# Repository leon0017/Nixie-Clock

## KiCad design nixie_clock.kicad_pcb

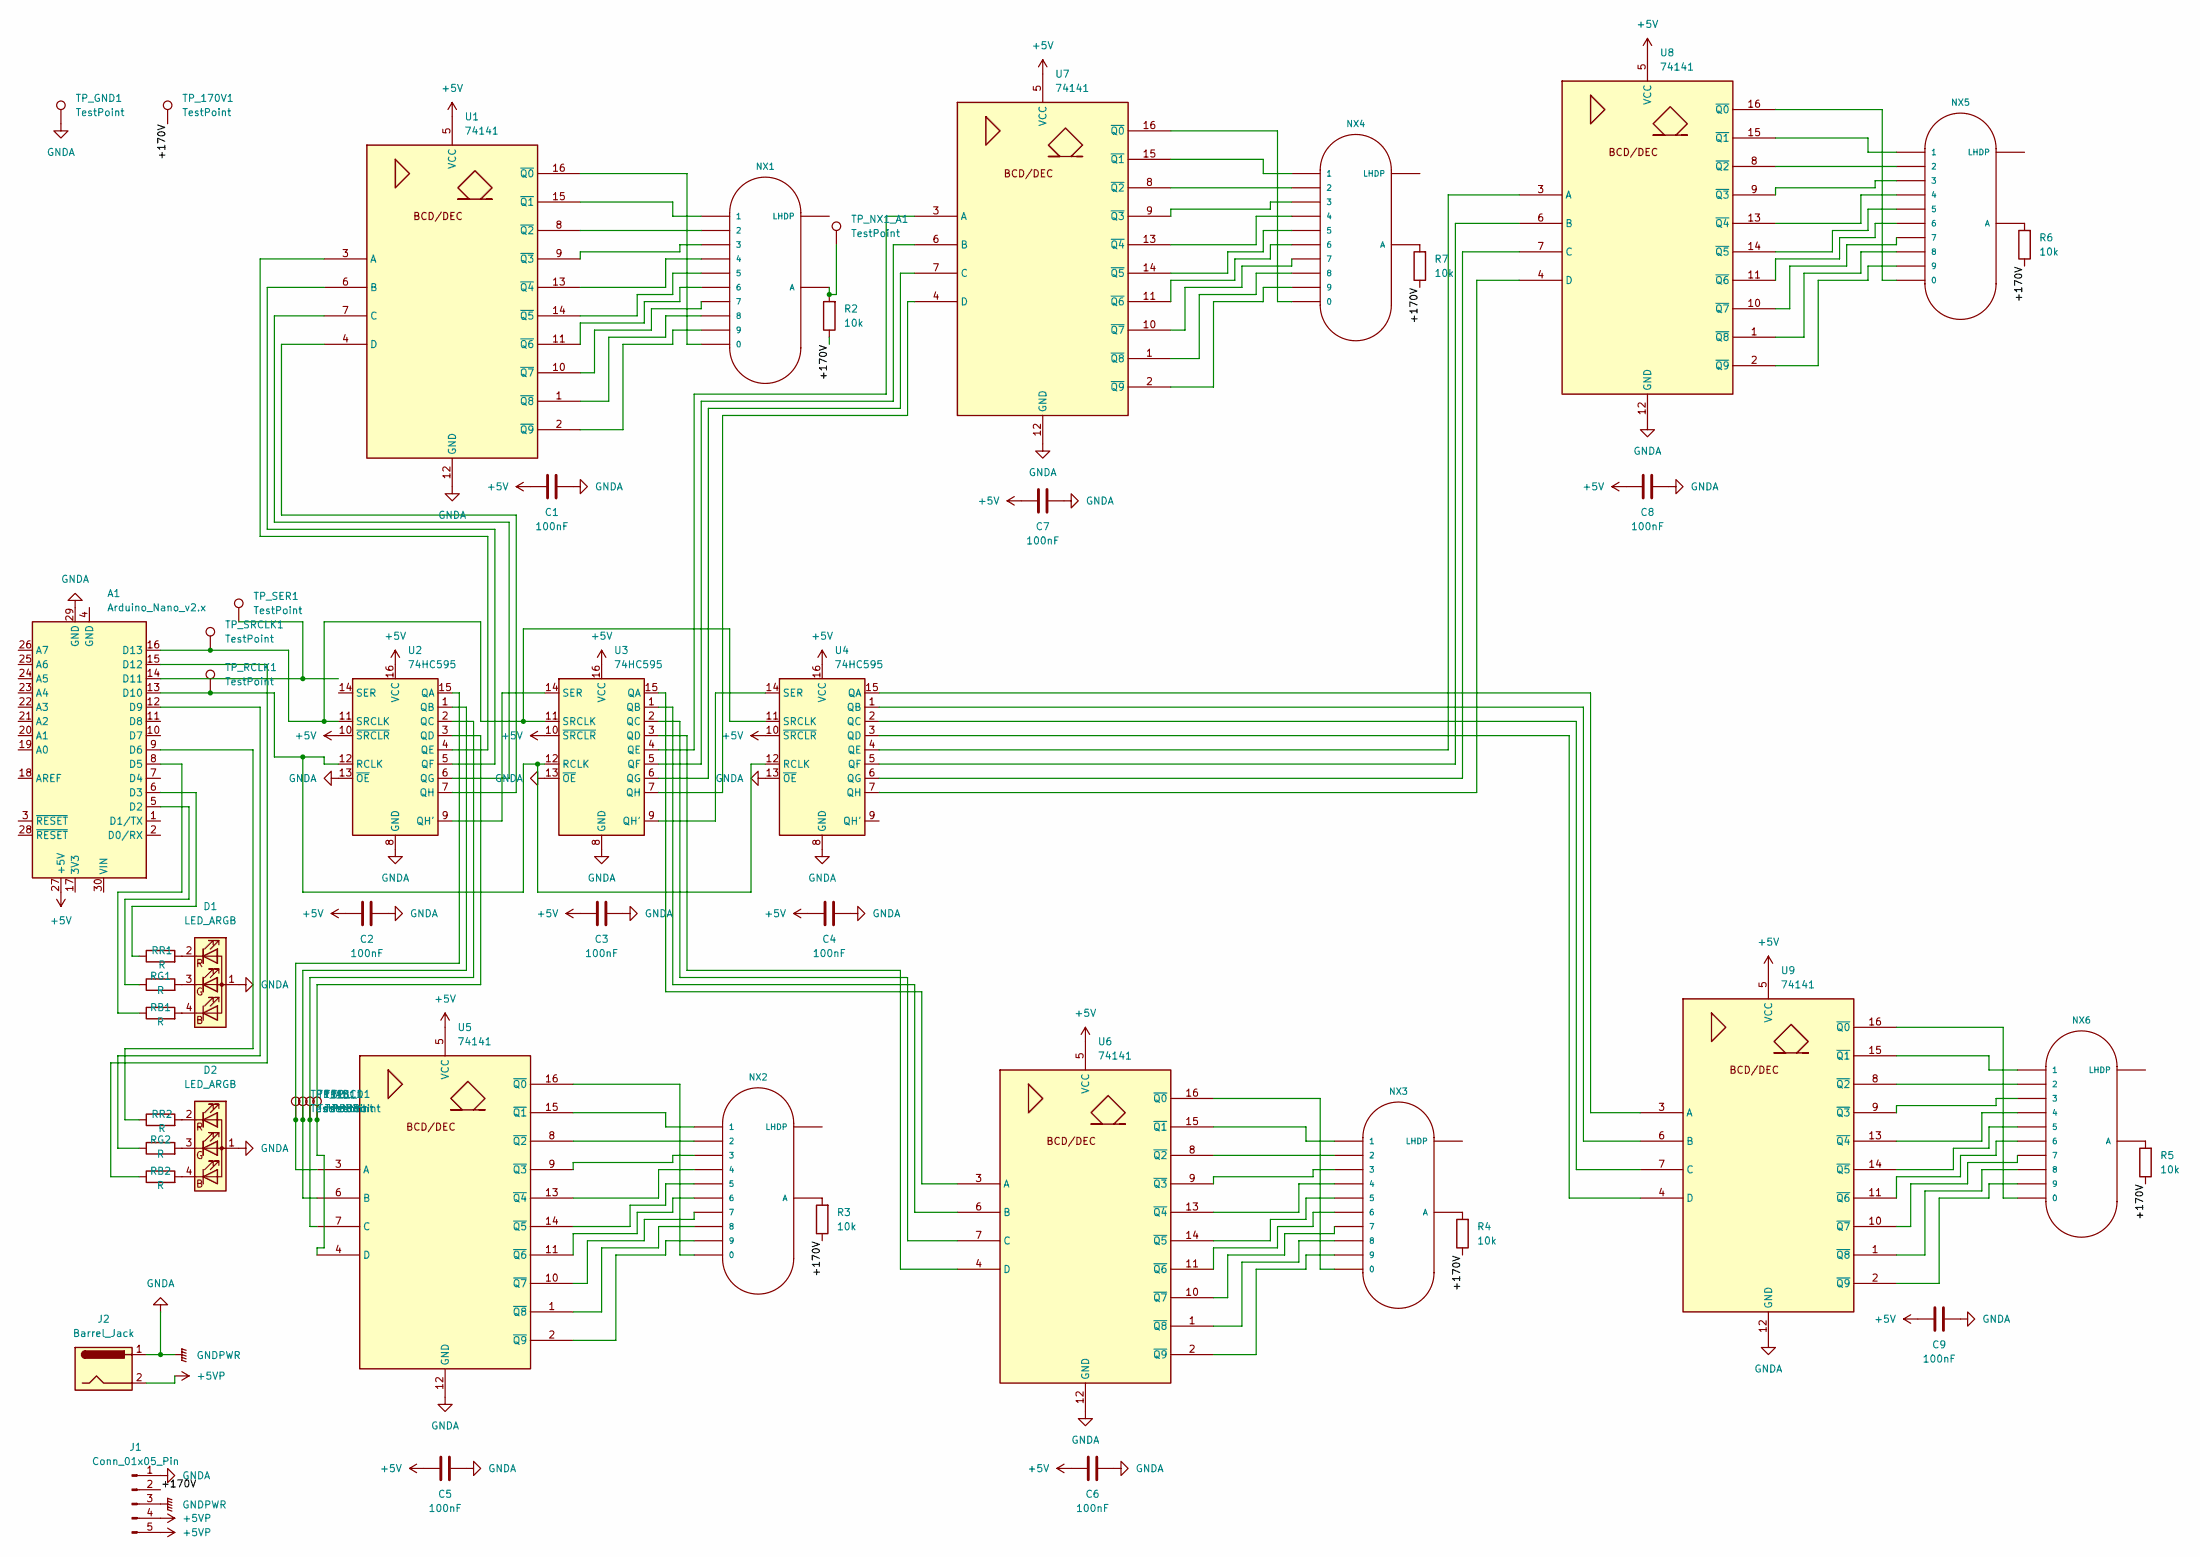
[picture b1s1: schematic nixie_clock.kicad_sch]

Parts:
A1: Arduino_Nano_v2.x; Arduino_Nano
C1, C2, C3, C4, C5, C6, C7, C8, C9: 100nF; C_Disc_D5.0mm_W2.5mm_P5.00mm
D1, D2: LED_ARGB; LED_D5.0mm-4_RGB
J1: Conn_01x05_Pin; AliStepUp
J2: Barrel_Jack; BarrelJack_Horizontal
NX1, NX2, NX3, NX4, NX5, NX6: IN-12BORIGINAL; nixies-us-IN-12
R2, R3, R4, R5, R6, R7: 10k; R_Axial_DIN0207_L6.3mm_D2.5mm_P10.16mm_Horizontal
RB1, RB2: R; R_Axial_DIN0207_L6.3mm_D2.5mm_P10.16mm_Horizontal
RG1, RG2: R; R_Axial_DIN0207_L6.3mm_D2.5mm_P10.16mm_Horizontal
RR1, RR2: R; R_Axial_DIN0207_L6.3mm_D2.5mm_P10.16mm_Horizontal
TP1_A1, TP1_B1, TP1_C1, TP1_D1: TestPoint; TestPoint_Pad_D1.0mm
TP_170V1: TestPoint; TestPoint_Pad_D1.0mm
TP_GND1: TestPoint; TestPoint_Pad_D1.0mm
TP_NX1_A1: TestPoint; TestPoint_Pad_D1.0mm
TP_RCLK1: TestPoint; TestPoint_Pad_D1.0mm
TP_SER1: TestPoint; TestPoint_Pad_D1.0mm
TP_SRCLK1: TestPoint; TestPoint_Pad_D1.0mm
U1, U5, U6, U7, U8, U9: 74141; DIP-16_W7.62mm
U2, U3, U4: 74HC595; DIP-16_W7.62mm

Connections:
+5V: A1.27 (+5V), C1.1, C2.1, C3.1, C4.1, C5.1, C6.1, C7.1, C8.1, C9.1, U1.5 (VCC), U2.10 (~SRCLR), U2.16 (VCC), U3.10 (~SRCLR), U3.16 (VCC), U4.10 (~SRCLR), U4.16 (VCC), U5.5 (VCC), U6.5 (VCC), U7.5 (VCC), U8.5 (VCC), U9.5 (VCC)
+5VP: J1.4, J1.5, J2.2
/+170V: J1.2, R2.1, R3.1, R4.1, R5.1, R6.1, R7.1, TP_170V1.1 (1_1)
GNDA: A1.29 (GND), C1.2, C2.2, C3.2, C4.2, C5.2, C6.2, C7.2, C8.2, C9.2, D1.1 (A), D2.1 (A), J1.1, J1.3, J2.1, TP_GND1.1 (1_1), U1.12 (GND), U2.8 (GND), U2.13 (~OE), U3.8 (GND), U3.13 (~OE), U4.8 (GND), U4.13 (~OE), U5.12 (GND), U6.12 (GND), U7.12 (GND), U8.12 (GND), U9.12 (GND)
unnamed: A1.5 (D2), RG1.1
unnamed: A1.6 (D3), RR1.1
unnamed: A1.8 (D5), RB1.1
unnamed: A1.9 (D6), RR2.1
unnamed: A1.12 (D9), RG2.1
unnamed: A1.13 (D10), TP_RCLK1.1 (1_1), U2.12 (RCLK), U3.12 (RCLK), U4.12 (RCLK)
unnamed: A1.14 (D11), TP_SER1.1 (1_1)
unnamed: A1.15 (D12), RB2.1
unnamed: A1.16 (D13), TP_SRCLK1.1 (1_1), U2.11 (SRCLK), U3.11 (SRCLK), U4.11 (SRCLK)
unnamed: D1.4 (BK), RB1.2
unnamed: D1.3 (GK), RG1.2
unnamed: D1.2 (RK), RR1.2
unnamed: D2.4 (BK), RB2.2
unnamed: D2.3 (GK), RG2.2
unnamed: D2.2 (RK), RR2.2
unnamed: NX1.A, R2.2, TP_NX1_A1.1 (1_1)
unnamed: NX2.A, R3.2
unnamed: NX3.A, R4.2
unnamed: NX4.A, R7.2
unnamed: NX5.A, R6.2
unnamed: NX6.A, R5.2
unnamed: U1.3 (A), U2.4 (QE)
unnamed: U1.6 (B), U2.5 (QF)
unnamed: U1.7 (C), U2.6 (QG)
unnamed: U1.4 (D), U2.7 (QH)
unnamed: NX1.0, U1.16 (~Q0)
unnamed: NX1.1, U1.15 (~Q1)
unnamed: NX1.2, U1.8 (~Q2)
unnamed: NX1.3, U1.9 (~Q3)
unnamed: NX1.4, U1.13 (~Q4)
unnamed: NX1.5, U1.14 (~Q5)
unnamed: NX1.6, U1.11 (~Q6)
unnamed: NX1.7, U1.10 (~Q7)
unnamed: NX1.8, U1.1 (~Q8)
unnamed: NX1.9, U1.2 (~Q9)
unnamed: TP1_A1.1 (1_1), U2.15 (QA), U5.3 (A)
unnamed: TP1_B1.1 (1_1), U2.1 (QB), U5.6 (B)
unnamed: TP1_C1.1 (1_1), U2.2 (QC), U5.7 (C)
unnamed: TP1_D1.1 (1_1), U2.3 (QD), U5.4 (D)
unnamed: U2.9 (QH'), U3.14 (SER)
unnamed: U3.15 (QA), U6.3 (A)
unnamed: U3.1 (QB), U6.6 (B)
unnamed: U3.2 (QC), U6.7 (C)
unnamed: U3.3 (QD), U6.4 (D)
unnamed: U3.4 (QE), U7.3 (A)
unnamed: U3.5 (QF), U7.6 (B)
unnamed: U3.6 (QG), U7.7 (C)
unnamed: U3.9 (QH'), U4.14 (SER)
unnamed: U3.7 (QH), U7.4 (D)
unnamed: U4.15 (QA), U9.3 (A)
unnamed: U4.1 (QB), U9.6 (B)
unnamed: U4.2 (QC), U9.7 (C)
unnamed: U4.3 (QD), U9.4 (D)
unnamed: U4.4 (QE), U8.3 (A)
unnamed: U4.5 (QF), U8.6 (B)
unnamed: U4.6 (QG), U8.7 (C)
unnamed: U4.7 (QH), U8.4 (D)
unnamed: NX2.0, U5.16 (~Q0)
unnamed: NX2.1, U5.15 (~Q1)
unnamed: NX2.2, U5.8 (~Q2)
unnamed: NX2.3, U5.9 (~Q3)
unnamed: NX2.4, U5.13 (~Q4)
unnamed: NX2.5, U5.14 (~Q5)
unnamed: NX2.6, U5.11 (~Q6)
unnamed: NX2.7, U5.10 (~Q7)
unnamed: NX2.8, U5.1 (~Q8)
unnamed: NX2.9, U5.2 (~Q9)
unnamed: NX3.0, U6.16 (~Q0)
unnamed: NX3.1, U6.15 (~Q1)
unnamed: NX3.2, U6.8 (~Q2)
unnamed: NX3.3, U6.9 (~Q3)
unnamed: NX3.4, U6.13 (~Q4)
unnamed: NX3.5, U6.14 (~Q5)
unnamed: NX3.6, U6.11 (~Q6)
unnamed: NX3.7, U6.10 (~Q7)
unnamed: NX3.8, U6.1 (~Q8)
unnamed: NX3.9, U6.2 (~Q9)
unnamed: NX4.0, U7.16 (~Q0)
unnamed: NX4.1, U7.15 (~Q1)
unnamed: NX4.2, U7.8 (~Q2)
unnamed: NX4.3, U7.9 (~Q3)
unnamed: NX4.4, U7.13 (~Q4)
unnamed: NX4.5, U7.14 (~Q5)
unnamed: NX4.6, U7.11 (~Q6)
unnamed: NX4.7, U7.10 (~Q7)
unnamed: NX4.8, U7.1 (~Q8)
unnamed: NX4.9, U7.2 (~Q9)
unnamed: NX5.0, U8.16 (~Q0)
unnamed: NX5.1, U8.15 (~Q1)
unnamed: NX5.2, U8.8 (~Q2)
unnamed: NX5.3, U8.9 (~Q3)
unnamed: NX5.4, U8.13 (~Q4)
unnamed: NX5.5, U8.14 (~Q5)
unnamed: NX5.6, U8.11 (~Q6)
unnamed: NX5.7, U8.10 (~Q7)
unnamed: NX5.8, U8.1 (~Q8)
unnamed: NX5.9, U8.2 (~Q9)
unnamed: NX6.0, U9.16 (~Q0)
unnamed: NX6.1, U9.15 (~Q1)
unnamed: NX6.2, U9.8 (~Q2)
unnamed: NX6.3, U9.9 (~Q3)
unnamed: NX6.4, U9.13 (~Q4)
unnamed: NX6.5, U9.14 (~Q5)
unnamed: NX6.6, U9.11 (~Q6)
unnamed: NX6.7, U9.10 (~Q7)
unnamed: NX6.8, U9.1 (~Q8)
unnamed: NX6.9, U9.2 (~Q9)

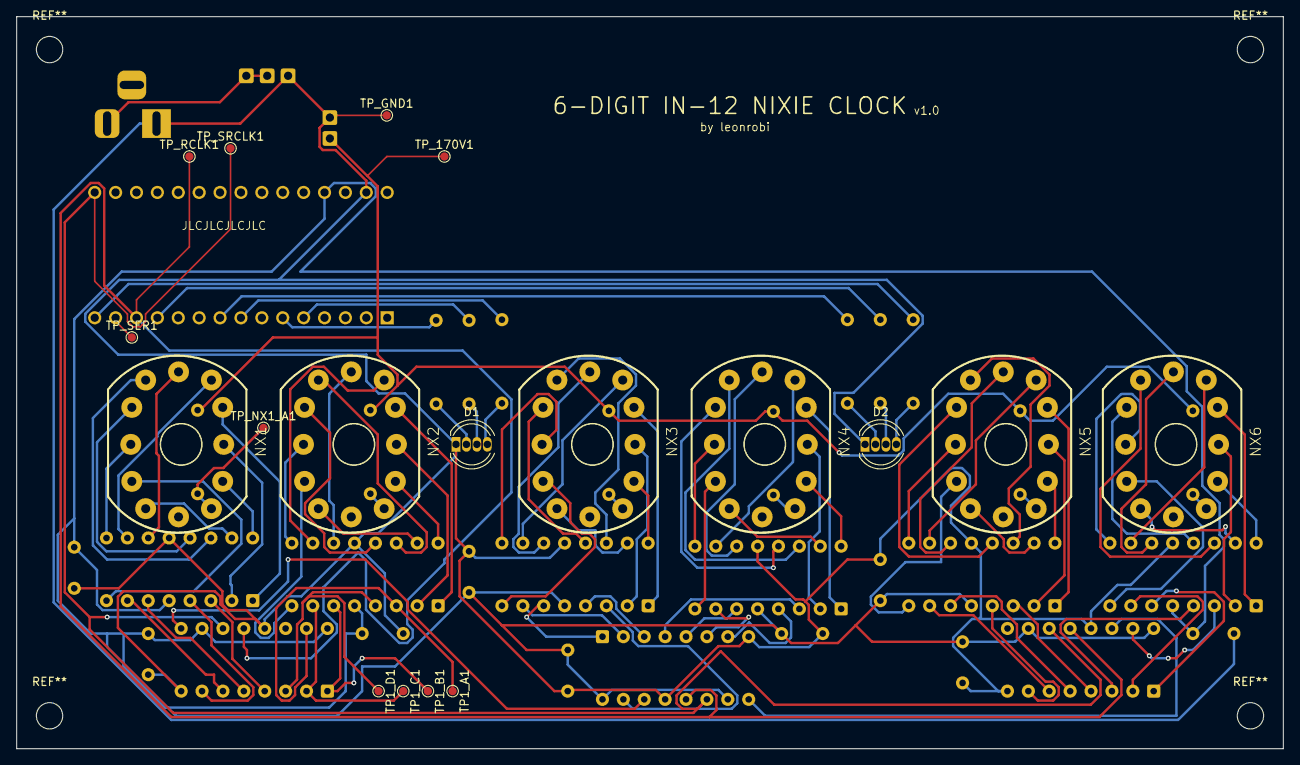
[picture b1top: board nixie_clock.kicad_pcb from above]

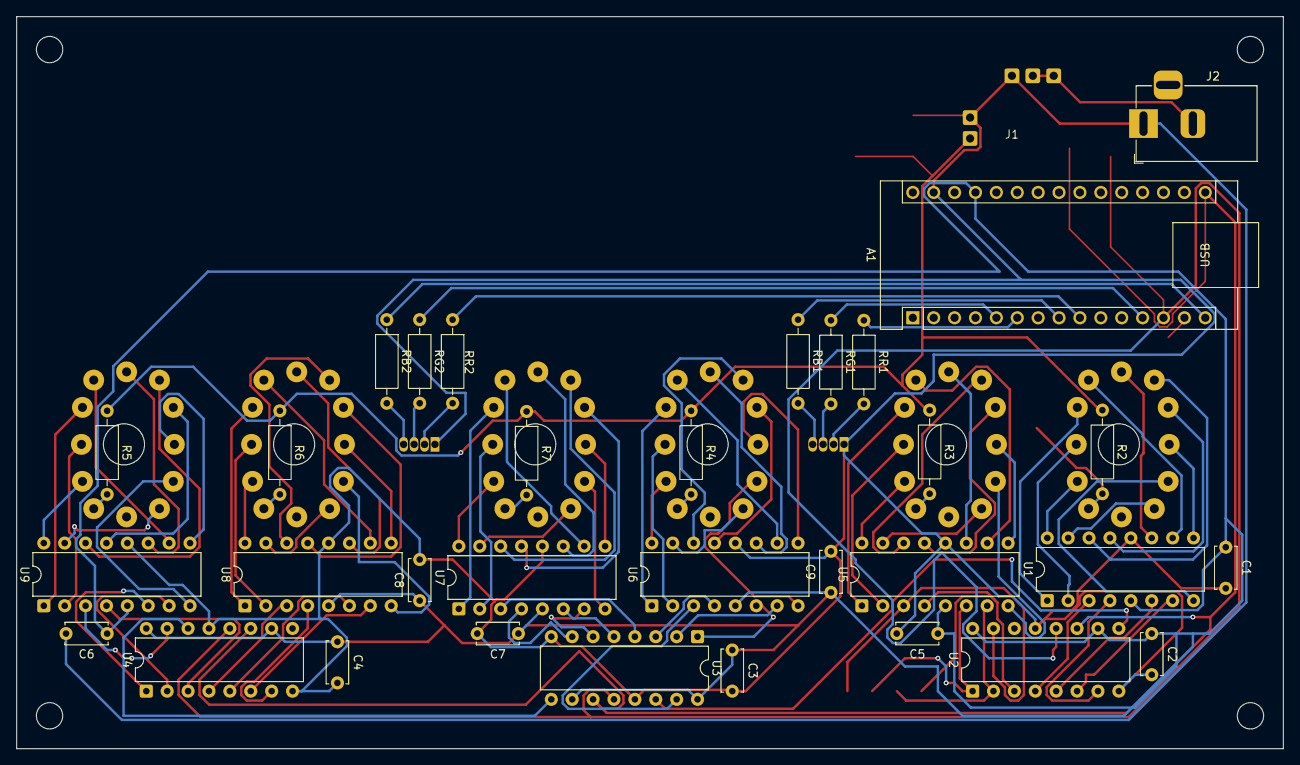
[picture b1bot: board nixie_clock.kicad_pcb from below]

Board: 2 copper layers, 154.0 x 89.0 mm, 51 parts (33 on the bottom side), 111 nets.
